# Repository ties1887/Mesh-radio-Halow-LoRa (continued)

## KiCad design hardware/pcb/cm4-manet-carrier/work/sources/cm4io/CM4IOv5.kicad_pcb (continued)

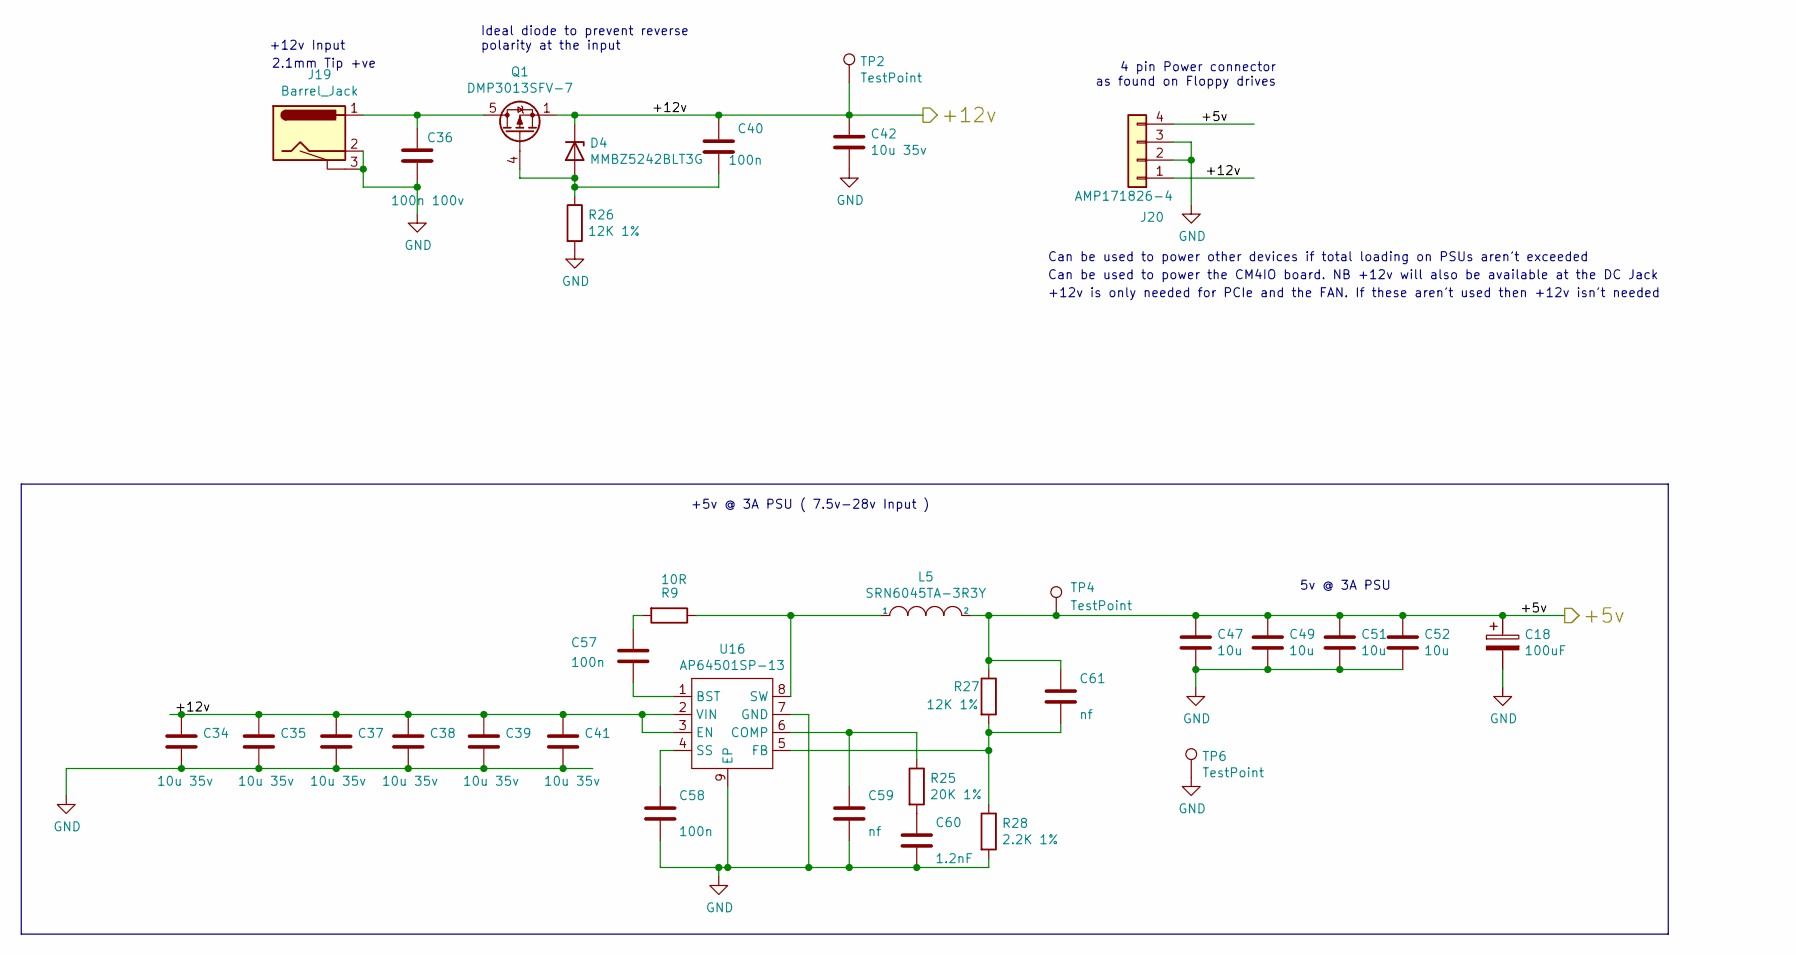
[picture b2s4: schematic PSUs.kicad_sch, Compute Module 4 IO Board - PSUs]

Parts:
C18: 100uF; CP_EIA-7343-31_Kemet-D; Part Description Capacitor, SP-Cap, 100u, 6.3V, 15mR ESR
C34, C35, C37, C38, C39, C41, C42: 10u 35v; C_0805_2012Metric; Part Description 10uF 10% or 20% 35V Ceramic Capacitor X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
C36: 100n 100v; C_0402_1005Metric; Part Description 0.1uF 10% 100V Ceramic Capacitor X5R 04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
C40, C57, C58: 100n; C_0402_1005Metric; Part Description 0.1uF 10% 16V Ceramic Capacitor X7R 040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
C47, C49, C51, C52: 10u; C_0805_2012Metric; Part Description 10uF 10% 10V Ceramic Capacitor X7R 0805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
C59: nf; C_0402_1005Metric
C60: 1.2nF; C_0402_1005Metric; Part Description 1200pF 10% 10V Ceramic Capacitor X5R 04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
C61: nf; C_0402_1005Metric; Part Description 220 pF, 50 V, 0402 [1005 Metric], ± 5%,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
D4: MMBZ5242BLT3G; D_SOT-23_ANK; Part Description Zener Diode 12V 225mW 5% Surface Mount 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
J19: Barrel_Jack; BarrelJack_Horizontal; Part Description DC Power Connectors PCB 2.1MM
J20: AMP171826-4; TE_171826-4; Part Description Wire-To-Board Connector, Right Angle, 2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
L5: SRN6045TA-3R3Y; L_Bourns_SRN6045TA; Part Description 3.3µH Semi-Shielded Wirewound Inductor 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
Q1: DMP3013SFV-7; Diodes_PowerDI3333-8; Part Description DMP3013SFV-7 - Power MOSFET, P Channel,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
R9: 10R; R_0402_1005Metric; Part Description Resistor 10R M1005 1% 63mW
R25: 20K 1%; R_0402_1005Metric; Part Description Resistor 20K M1005 1% 63mW
R26, R27: 12K 1%; R_0402_1005Metric; Part Description Resistor 12K M1005 1% 63mW
R28: 2.2K 1%; R_0402_1005Metric; Part Description Resistor 2.2K M1005 1% 63mW
TP2, TP4, TP6: TestPoint; TestPoint_Pad_2.0x2.0mm
U16: AP64501SP-13; SOIC-8-1EP_3.9x4.9mm_P1.27mm_EP2.95x4.9mm_Mask2.71x3.4mm_Th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; Part Description Buck Switching Regulator IC Positive Ad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

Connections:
/+5v: C18.1, C47.1, C49.1, C51.1, C52.1, C61.1, J20.4, L5.2, R27.1, TP4.1; also elsewhere on the board
/+12v: C34.1, C35.1, C37.1, C38.1, C39.1, C40.1, C41.1, C42.1, D4.1 (K), J20.1, Q1.1 (S), Q1.2 (S), Q1.3 (S), TP2.1, U16.2 (VIN), U16.3 (EN); also elsewhere on the board
GND: C18.2, C34.2, C35.2, C36.2, C37.2, C38.2, C39.2, C41.2, C42.2, C47.2, C49.2, C51.2, C52.2, C58.2, C59.2, C60.2, J19.2, J19.3, J20.2, J20.3, R26.2, R28.2, TP6.1, U16.7 (GND), U16.9 (EP); also elsewhere on the board
unnamed: C36.1, J19.1, Q1.5 (D)
unnamed: C40.2, D4.2 (A), Q1.4 (G), R26.1
unnamed: C57.1, R9.2
unnamed: C57.2, U16.1 (BST)
unnamed: C58.1, U16.4 (SS)
unnamed: C59.1, R25.1, U16.6 (COMP)
unnamed: C60.1, R25.2
unnamed: C61.2, R27.2, R28.1, U16.5 (FB)
unnamed: L5.1, R9.1, U16.8 (SW)

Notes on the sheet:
+12v Input
Can be used to power other devices if total loading on PSUs aren't exceeded
5v @ 3A PSU
+12v is only needed for PCIe and the FAN. If these aren't used then +12v isn't needed
Can be used to power the CM4IO board. NB +12v will also be available at the DC Jack
2.1mm Tip +ve
Ideal diode to prevent reverse polarity at the input
4 pin Power connector as found on Floppy drives
+5v @ 3A PSU ( 7.5v-28v Input )

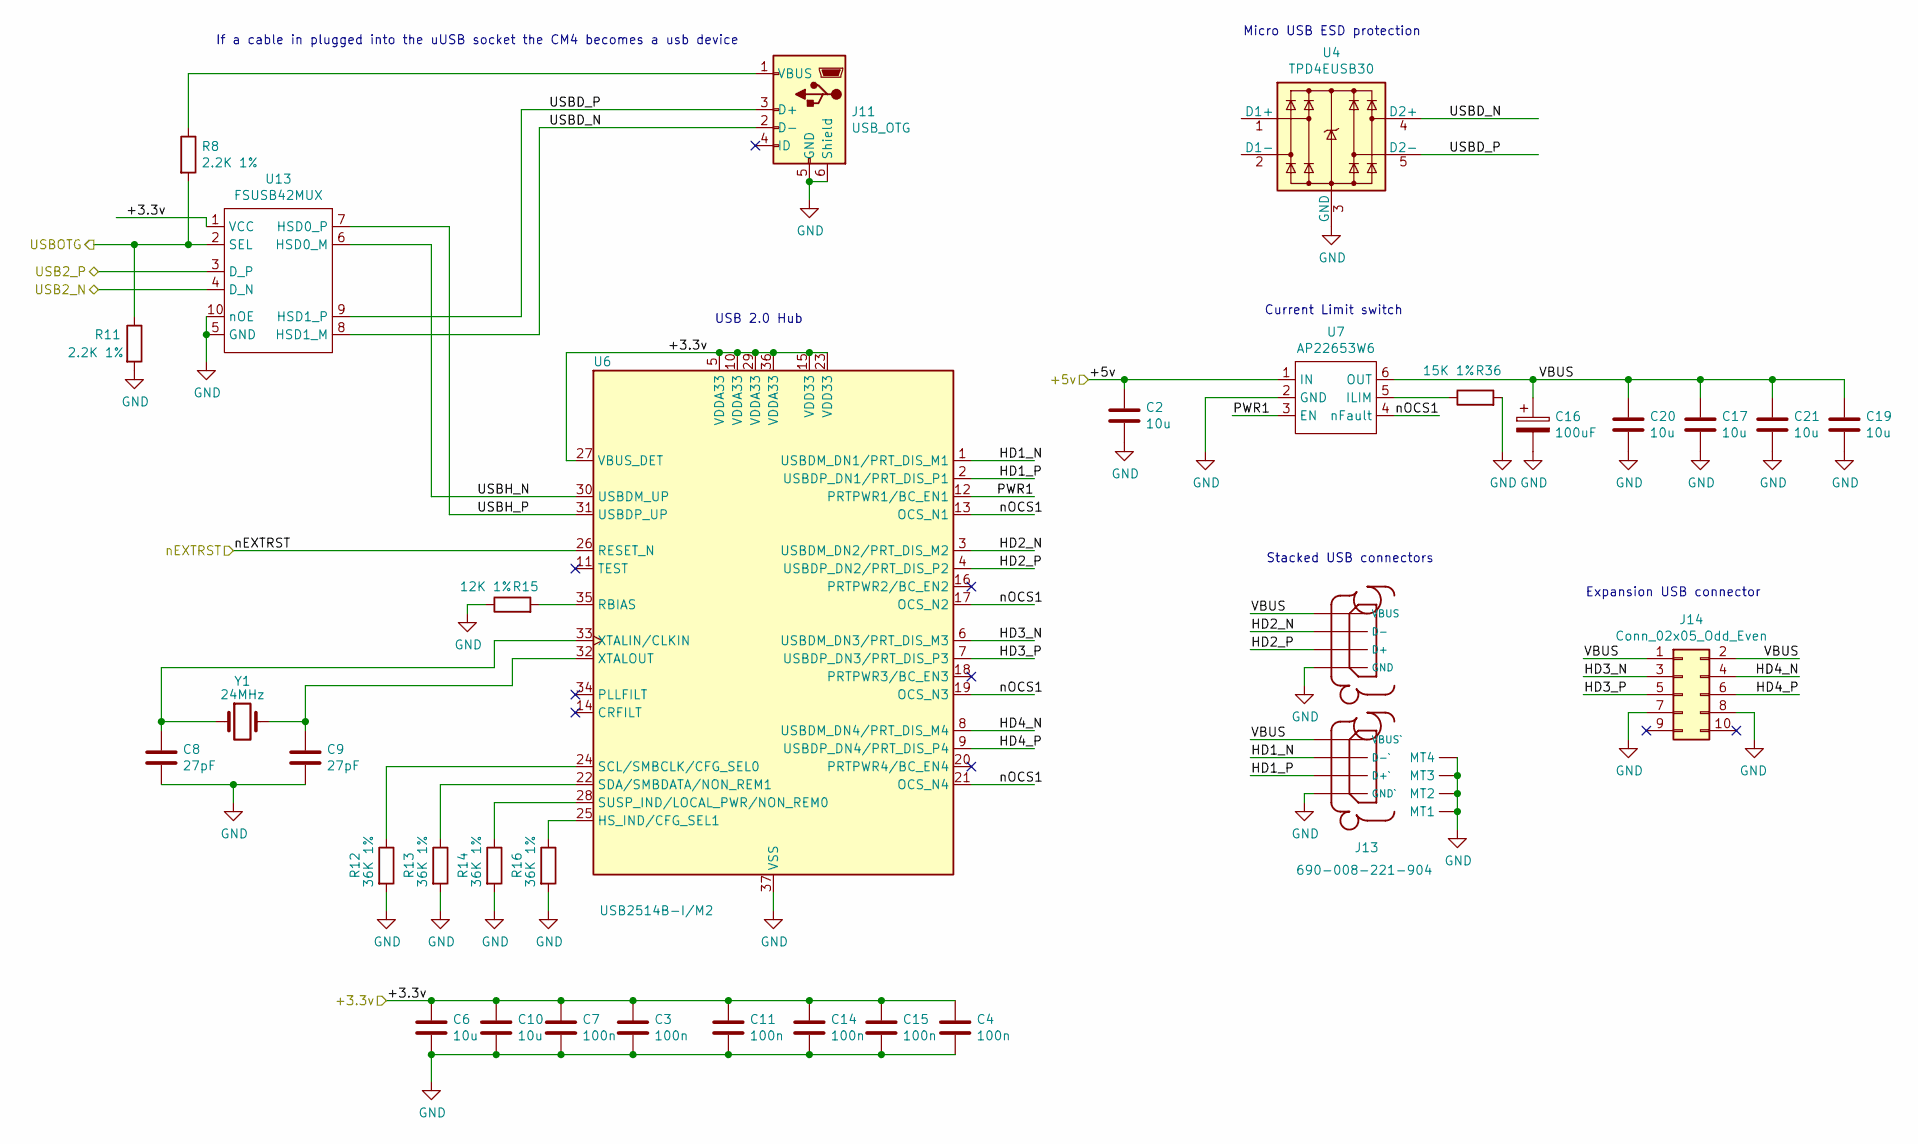
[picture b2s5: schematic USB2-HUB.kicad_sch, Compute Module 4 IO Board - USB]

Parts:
C2, C6, C10, C17, C19, C20, C21: 10u; C_0805_2012Metric; Part Description 10uF 10% 10V Ceramic Capacitor X7R 0805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
C3, C4, C7, C11, C14, C15: 100n; C_0402_1005Metric; Part Description 0.1uF 10% 16V Ceramic Capacitor X7R 040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
C8, C9: 27pF; C_0402_1005Metric; Part Description 27pF 5% 50V Ceramic Capacitor C0G, NP0 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
C16: 100uF; CP_EIA-7343-31_Kemet-D; Part Description Capacitor, SP-Cap, 100u, 6.3V, 15mR ESR
J11: USB_OTG; USB_Micro-B_EDAC_UCON00686; Part Description USB - micro B USB 2.0 Receptacle Connec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
J13: 690-008-221-904; MOLEX_USB_67298-4090; Part Description USB-A (USB TYPE-A), Stacked Receptacle 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
J14: Conn_02x05_Odd_Even; PinHeader_2x05_P2.54mm_Vertical; Part Description PinHeader_2x05_P2.54mm_Vertical
R8, R11: 2.2K 1%; R_0402_1005Metric; Part Description Resistor 2.2K M1005 1% 63mW
R12, R13, R14, R16: 36K 1%; R_0402_1005Metric; Part Description Resistor 36K M1005 1% 63mW
R15: 12K 1%; R_0402_1005Metric; Part Description Resistor 12K M1005 1% 63mW
R36: 15K 1%; R_0402_1005Metric; Part Description Resistor 15K M1005 1% 63mW
U4: TPD4EUSB30; USON-10_2.5x1.0mm_P0.5mm; Part Description Quad TVS diode for high speed signals (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
U6: USB2514B-I/M2; QFN-36-1EP_6x6mm_P0.5mm_EP3.7x3.7mm; Part Description USB Hub Controller USB Interface 36-SQF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
U7: AP22653W6; SOT-23-6; Part Description Power Switch/Driver 1:1 P-Channel 2.1A 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
U13: FSUSB42MUX; MSOP-10_3x3mm_P0.5mm; Part Description USB Switch IC 1 Channel 10-MSOP
Y1: 24MHz; Crystal_SMD_HC49-SD; Part Description 24MHz Crystal 18pf 30ppm 30ppm

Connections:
/+3.3v: C3.1, C4.1, C6.1, C7.1, C10.1, C11.1, C14.1, C15.1, U6.5 (VDDA33), U6.10 (VDDA33), U6.15 (VDD33), U6.23 (VDD33), U6.27 (VBUS_DET), U6.29 (VDDA33), U6.36 (VDDA33), U13.1 (VCC); also elsewhere on the board
/+5v: C2.1, U7.1 (IN); also elsewhere on the board
/CM4_HighSpeed/USB2_N: U13.4 (D_N); also elsewhere on the board
/CM4_HighSpeed/USB2_P: U13.3 (D_P); also elsewhere on the board
/CM4_HighSpeed/USBOTG_ID: R8.2, R11.1, U13.2 (SEL); also elsewhere on the board
/USB2-HUB/HD1_N: J13.2 (D-`), U6.1 (USBDM_DN1/PRT_DIS_M1)
/USB2-HUB/HD1_P: J13.3 (D+`), U6.2 (USBDP_DN1/PRT_DIS_P1)
/USB2-HUB/HD2_N: J13.6 (D-), U6.3 (USBDM_DN2/PRT_DIS_M2)
/USB2-HUB/HD2_P: J13.7 (D+), U6.4 (USBDP_DN2/PRT_DIS_P2)
/USB2-HUB/HD3_N: J14.3, U6.6 (USBDM_DN3/PRT_DIS_M3)
/USB2-HUB/HD3_P: J14.5, U6.7 (USBDP_DN3/PRT_DIS_P3)
/USB2-HUB/HD4_N: J14.4, U6.8 (USBDM_DN4/PRT_DIS_M4)
/USB2-HUB/HD4_P: J14.6, U6.9 (USBDP_DN4/PRT_DIS_P4)
/USB2-HUB/PWR1: U6.12 (PRTPWR1/BC_EN1), U7.3 (EN)
/USB2-HUB/USBD_N: J11.2 (D-), U4.4 (D2+), U4.7, U13.8 (HSD1_M)
/USB2-HUB/USBD_P: J11.3 (D+), U4.5 (D2-), U4.6, U13.9 (HSD1_P)
/USB2-HUB/USBH_N: U6.30 (USBDM_UP), U13.6 (HSD0_M)
/USB2-HUB/USBH_P: U6.31 (USBDP_UP), U13.7 (HSD0_P)
/USB2-HUB/VBUS: C16.1, C17.1, C19.1, C20.1, C21.1, J13.1 (VBUS`), J13.5 (VBUS), J14.1, J14.2, U7.6 (OUT)
/USB2-HUB/nOCS1: U6.13 (OCS_N1), U6.17 (OCS_N2), U6.19 (OCS_N3), U6.21 (OCS_N4), U7.4 (nFault)
/nEXTRST: U6.26 (RESET_N); also elsewhere on the board
GND: C2.2, C3.2, C4.2, C6.2, C7.2, C8.2, C9.2, C10.2, C11.2, C14.2, C15.2, C16.2, C17.2, C19.2, C20.2, C21.2, J11.5 (GND), J11.6 (Shield), J13.4 (GND`), J13.8 (GND), J13.MT1, J13.MT2, J13.MT3, J13.MT4, J14.7, J14.8, R11.2, R12.2, R13.2, R14.2, R15.1, R16.2, R36.2, U4.3 (GND), U4.8 (GND), U6.37 (VSS), U7.2 (GND), U13.5 (GND), U13.10 (nOE); also elsewhere on the board
unnamed: C8.1, U6.33 (XTALIN/CLKIN), Y1.1
unnamed: C9.1, U6.32 (XTALOUT), Y1.2
unnamed: J11.1 (VBUS), R8.1
unnamed: R12.1, U6.24 (SCL/SMBCLK/CFG_SEL0)
unnamed: R13.1, U6.22 (SDA/SMBDATA/NON_REM1)
unnamed: R14.1, U6.28 (SUSP_IND/LOCAL_PWR/NON_REM0)
unnamed: R15.2, U6.35 (RBIAS)
unnamed: R16.1, U6.25 (HS_IND/CFG_SEL1)
unnamed: R36.1, U7.5 (ILIM)
unnamed: U4.1 (D1+), U4.10
unnamed: U4.2 (D1-), U4.9

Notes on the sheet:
Expansion USB connector
Current Limit switch
USB 2.0 Hub
If a cable in plugged into the uUSB socket the CM4 becomes a usb device
Micro USB ESD protection
Stacked USB connectors

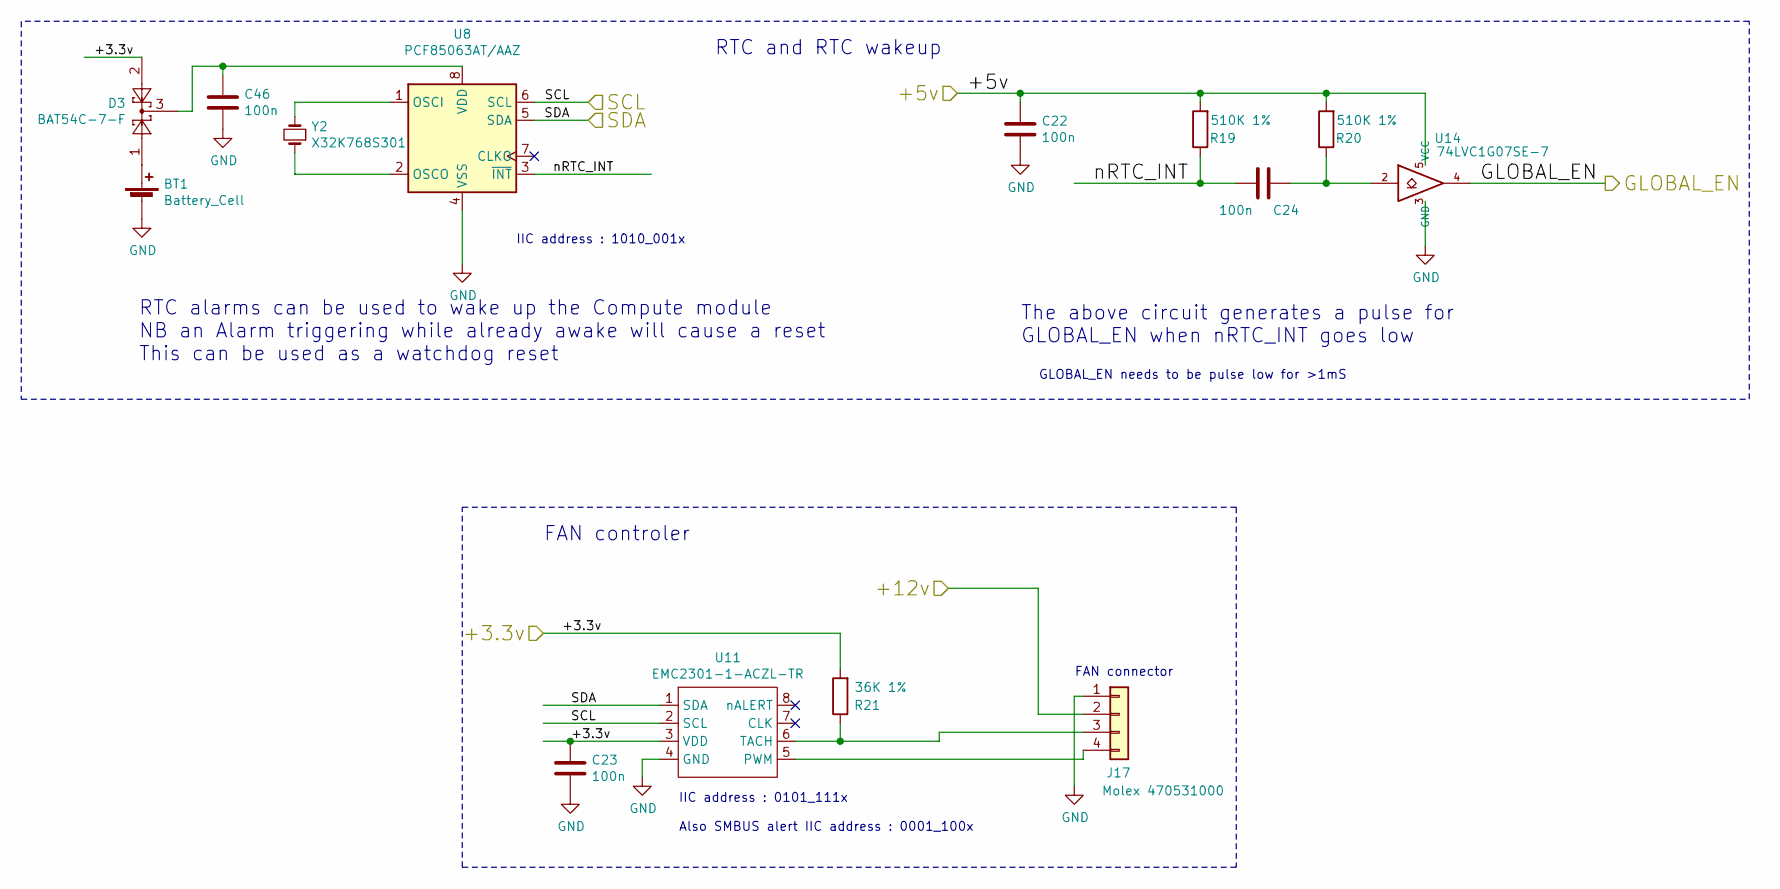
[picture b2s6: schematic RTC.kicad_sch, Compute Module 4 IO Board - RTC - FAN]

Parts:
BT1: Battery_Cell; BatteryHolder_Keystone_3034_1x20mm; Part Description Battery Retainer Coin, 20.0mm 1 Cell SM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
C22, C23, C24, C46: 100n; C_0402_1005Metric; Part Description 0.1uF 10% 16V Ceramic Capacitor X7R 040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
D3: BAT54C-7-F; SOT-23; Part Description Diode Array 1 Pair Common Cathode Schot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
J17: Molex 470531000; FanPinHeader_1x04_P2.54mm_Vertical; Part Description Connector Header Through Hole 4 positio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
R19, R20: 510K 1%; R_0402_1005Metric; Part Description Resistor 510K M1005 1% 63mW
R21: 36K 1%; R_0402_1005Metric; Part Description Resistor 36K M1005 1% 63mW
U8: PCF85063AT/AAZ; SOIC-8_3.9x4.9mm_P1.27mm; Part Description Real Time Clock (RTC) IC Clock/Calendar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
U11: EMC2301-1-ACZL-TR; MSOP-8_3x3mm_P0.65mm; Part Description Motor Driver PWM 8-MSOP
U14: 74LVC1G07SE-7; SOT-353_SC-70-5; Part Description Buffer, Non-Inverting 1 Element 1 Bit p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
Y2: X32K768S301; Crystal_SMD_3215-2Pin_3.2x1.5mm; Part Description Crystal 32.768KHz 7pF 20pmm

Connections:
/+3.3v: C23.1, D3.2, R21.2, U11.3 (VDD); also elsewhere on the board
/+5v: C22.1, R19.2, R20.2, U14.5 (VCC); also elsewhere on the board
/+12v: J17.2; also elsewhere on the board
/CM4_GPIO ( Ethernet, GPIO, SDCARD)/GLOBAL_EN: U14.4; also elsewhere on the board
/CM4_HighSpeed/SCL0: U8.6 (SCL), U11.2 (SCL); also elsewhere on the board
/CM4_HighSpeed/SDA0: U8.5 (SDA), U11.1 (SDA); also elsewhere on the board
/RTC , Wakeup, FAN/nRTC_INT: C24.2, R19.1, U8.3 (~INT)
GND: BT1.2 (-), C22.2, C23.2, C46.2, J17.1, U8.4 (VSS), U11.4 (GND), U14.3 (GND); also elsewhere on the board
unnamed: BT1.1 (+), D3.1
unnamed: C24.1, R20.1, U14.2
unnamed: C46.1, D3.3, U8.8 (VDD)
unnamed: J17.3, R21.1, U11.6 (TACH)
unnamed: J17.4, U11.5 (PWM)
unnamed: U8.1 (OSCI), Y2.2
unnamed: U8.2 (OSCO), Y2.1

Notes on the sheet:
RTC alarms can be used to wake up the Compute module NB an Alarm triggering while already awake will cause a reset This can be used as a watchdog reset
RTC and RTC wakeup
Also SMBUS alert IIC address : 0001_100x
IIC address : 0101_111x
IIC address : 1010_001x
GLOBAL_EN needs to be pulse low for >1mS
FAN controler
FAN connector
The above circuit generates a pulse for GLOBAL_EN when nRTC_INT goes low

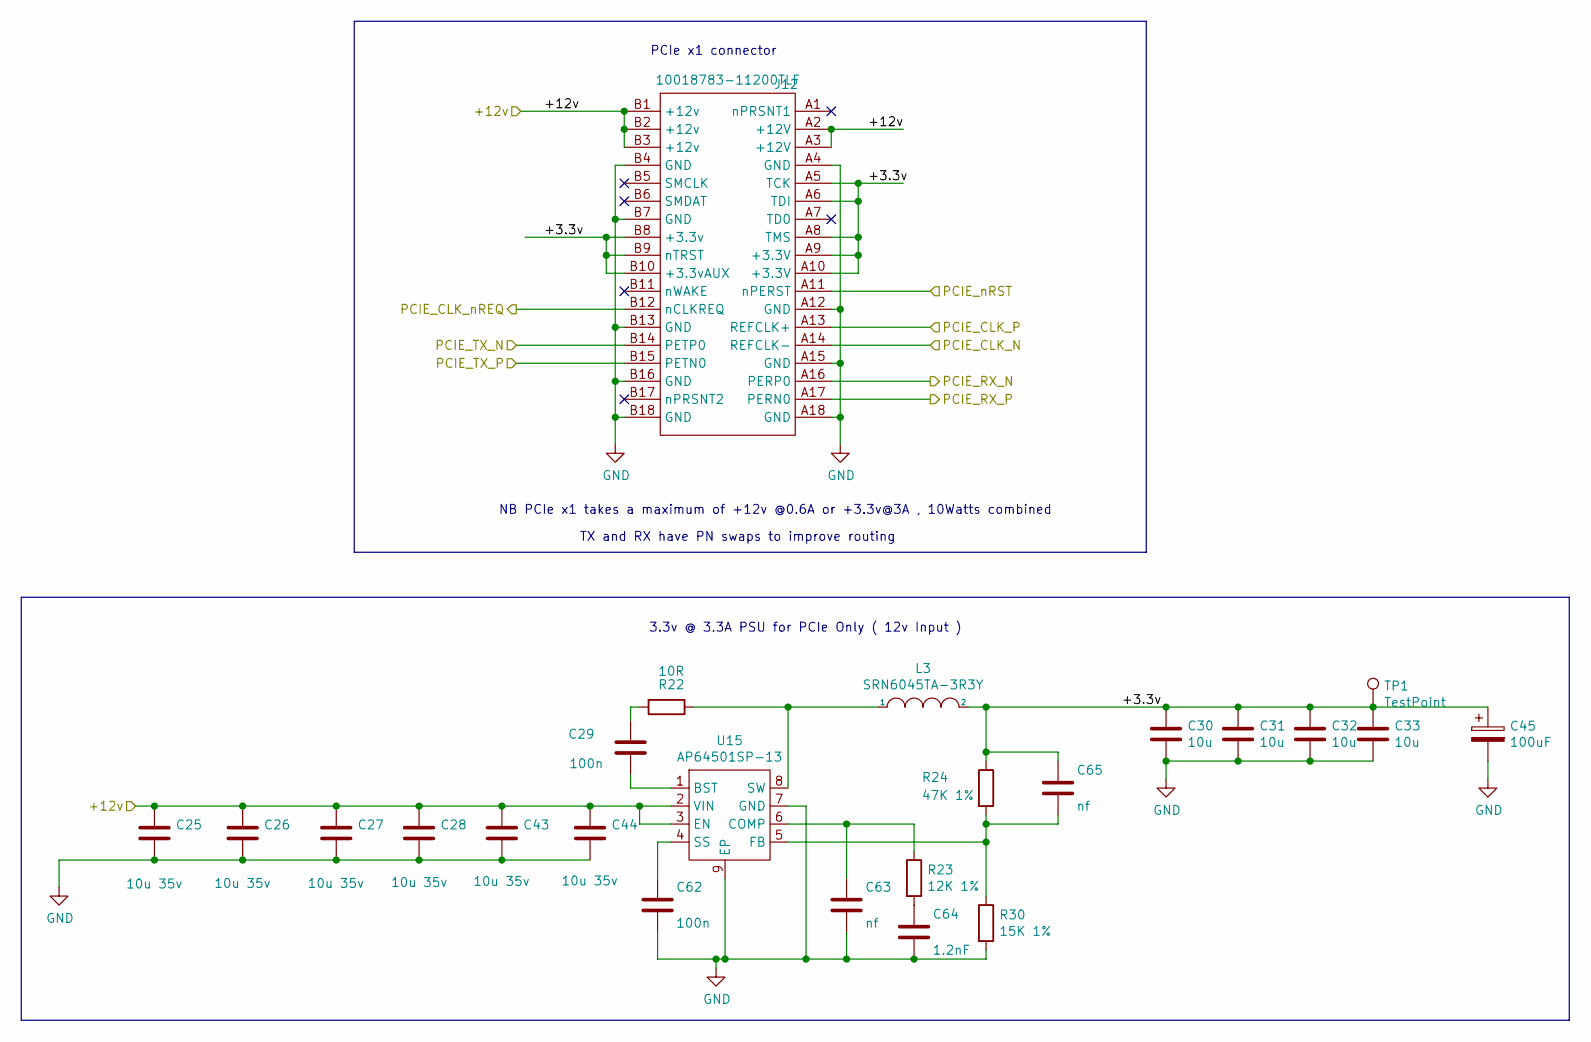
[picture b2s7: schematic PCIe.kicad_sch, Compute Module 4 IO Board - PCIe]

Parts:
C25, C26, C27, C28, C43, C44: 10u 35v; C_0805_2012Metric; Part Description 10uF 10% or 20% 35V Ceramic Capacitor X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
C29, C62: 100n; C_0402_1005Metric; Part Description 0.1uF 10% 16V Ceramic Capacitor X7R 040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
C30, C31, C32, C33: 10u; C_0805_2012Metric; Part Description 10uF 10% 10V Ceramic Capacitor X7R 0805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
C45: 100uF; CP_EIA-7343-31_Kemet-D; Part Description Capacitor, SP-Cap, 100u, 6.3V, 15mR ESR
C63: nf; C_0402_1005Metric
C64: 1.2nF; C_0402_1005Metric; Part Description 1200pF 10% 10V Ceramic Capacitor X5R 04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
C65: nf; C_0402_1005Metric; Part Description 27pF 5% 50V Ceramic Capacitor C0G, NP0 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
J12: 10018783-11200TLF; PCIex1-36; Part Description PCI Express/PCI Connectors PCIE THROUGH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
L3: SRN6045TA-3R3Y; L_Bourns_SRN6045TA; Part Description 3.3µH Semi-Shielded Wirewound Inductor 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
R22: 10R; R_0402_1005Metric; Part Description Resistor 10R M1005 1% 63mW
R23: 12K 1%; R_0402_1005Metric; Part Description Resistor 12K M1005 1% 63mW
R24: 47K 1%; R_0402_1005Metric; Part Description Resistor 47K M1005 1% 63mW
R30: 15K 1%; R_0402_1005Metric; Part Description Resistor 15K M1005 1% 63mW
TP1: TestPoint; TestPoint_Pad_2.0x2.0mm
U15: AP64501SP-13; SOIC-8-1EP_3.9x4.9mm_P1.27mm_EP2.95x4.9mm_Mask2.71x3.4mm_Th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; Part Description Buck Switching Regulator IC Positive Ad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

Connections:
/+12v: C25.1, C26.1, C27.1, C28.1, C43.1, C44.1, J12.A2 (+12V), J12.A3 (+12V), J12.B1 (+12v), J12.B2 (+12v), J12.B3 (+12v), U15.2 (VIN), U15.3 (EN); also elsewhere on the board
/CM4_HighSpeed/PCIE_CLK_N: J12.A14 (REFCLK-); also elsewhere on the board
/CM4_HighSpeed/PCIE_CLK_P: J12.A13 (REFCLK+); also elsewhere on the board
/CM4_HighSpeed/PCIE_CLK_nREQ: J12.B12 (nCLKREQ); also elsewhere on the board
/CM4_HighSpeed/PCIE_RX_N: J12.A16 (PERP0); also elsewhere on the board
/CM4_HighSpeed/PCIE_RX_P: J12.A17 (PERN0); also elsewhere on the board
/CM4_HighSpeed/PCIE_TX_N: J12.B14 (PETP0); also elsewhere on the board
/CM4_HighSpeed/PCIE_TX_P: J12.B15 (PETN0); also elsewhere on the board
/CM4_HighSpeed/PCIE_nRST: J12.A11 (nPERST); also elsewhere on the board
/PCIe-connector/+3.3v: C30.1, C31.1, C32.1, C33.1, C45.1, C65.1, J12.A5 (TCK), J12.A6 (TDI), J12.A8 (TMS), J12.A9 (+3.3V), J12.A10 (+3.3V), J12.B8 (+3.3v), J12.B9 (nTRST), J12.B10 (+3.3vAUX), L3.2, R24.1, TP1.1
GND: C25.2, C26.2, C27.2, C28.2, C30.2, C31.2, C32.2, C33.2, C43.2, C44.2, C45.2, C62.2, C63.2, C64.2, J12.A4 (GND), J12.A12 (GND), J12.A15 (GND), J12.A18 (GND), J12.B4 (GND), J12.B7 (GND), J12.B13 (GND), J12.B16 (GND), J12.B18 (GND), R30.2, U15.7 (GND), U15.9 (EP); also elsewhere on the board
unnamed: C29.1, R22.2
unnamed: C29.2, U15.1 (BST)
unnamed: C62.1, U15.4 (SS)
unnamed: C63.1, R23.1, U15.6 (COMP)
unnamed: C64.1, R23.2
unnamed: C65.2, R24.2, R30.1, U15.5 (FB)
unnamed: L3.1, R22.1, U15.8 (SW)

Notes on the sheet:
TX and RX have PN swaps to improve routing
PCIe x1 connector
3.3v @ 3.3A PSU for PCIe Only ( 12v Input )
NB PCIe x1 takes a maximum of +12v @0.6A or +3.3v@3A , 10Watts combined

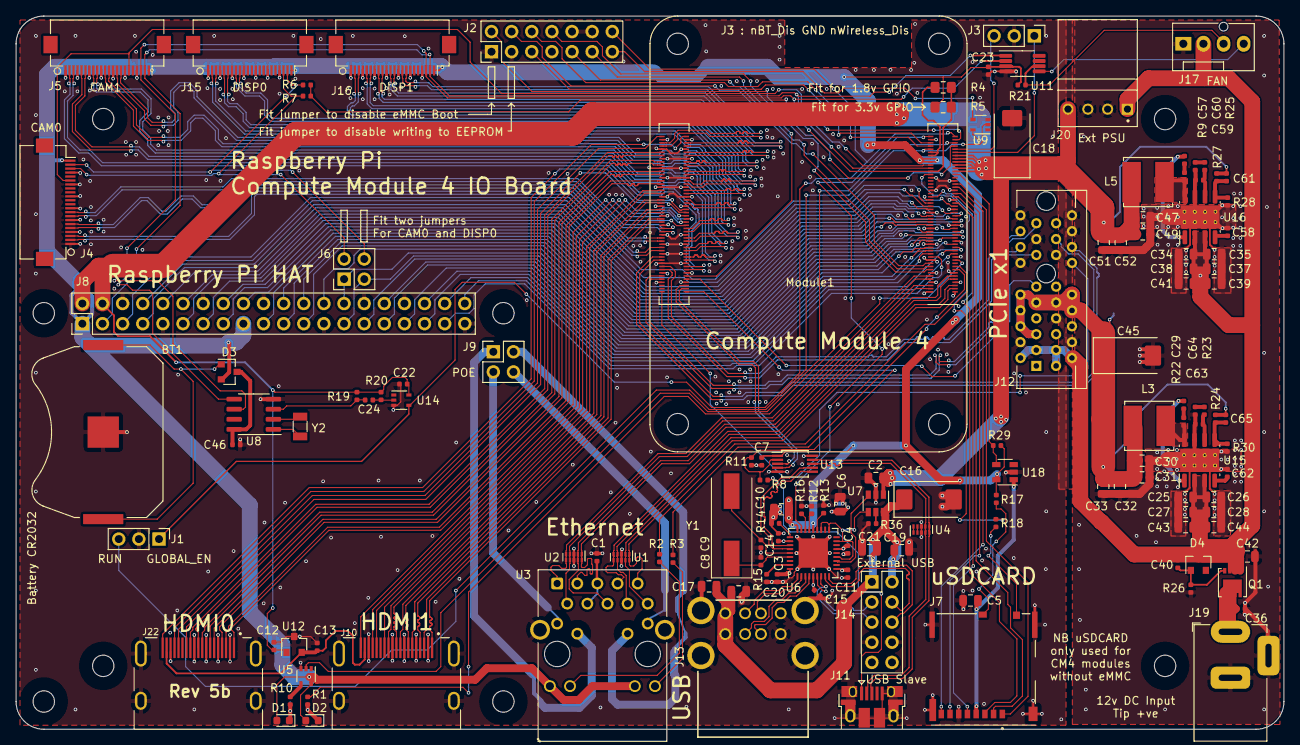
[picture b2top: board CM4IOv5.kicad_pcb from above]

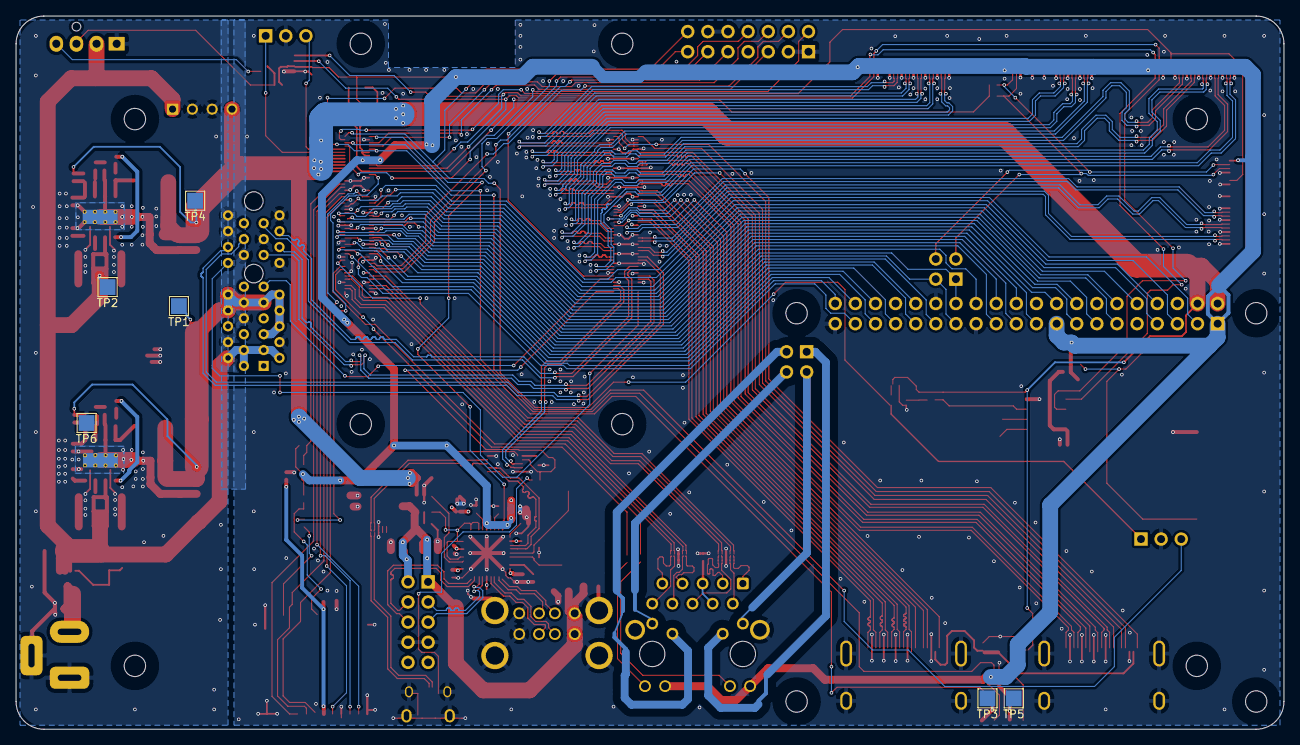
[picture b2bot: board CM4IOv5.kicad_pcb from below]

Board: 4 copper layers, 160.0 x 90.0 mm, 151 parts (6 on the bottom side), 204 nets.

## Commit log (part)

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2026-05-05 Add initial project documentation to README
    Added detailed project information including overview, features, hardware components, connectivity, power system, wiring, and build guide.
2026-05-05 Revise README to enhance project description
    Updated project description to clarify development status and author background.
2026-05-08 Add Bill of Materials documentation
    Added a detailed Bill of Materials for the core and power systems including parts, specifications, quantities, prices, and notes.
2026-05-08 Update README with full part list link
    Added link to full part list in README.
2026-05-23 Update README with simple system overview
2026-06-17 added simple wire diagram
2026-06-18 Add new images to README.md
2026-06-18 Create .README BEFORE BUILD
